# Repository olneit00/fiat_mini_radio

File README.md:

# PipER32 – Mini-Radio für den Fiat 500

**PipER32** ist ein kompaktes, selbst gebautes Internetradio im Stil klassischer Autoradios der 1960er-Jahre. Das Projekt verbindet ein individuell konstruiertes, 3D-druckbares Gehäuse mit moderner Elektronik und einer bewusst zurückhaltenden Retro-Optik.

Das Gerät ist für den Einbau in einen kleinen vorhandenen Aschenbecher-Schacht eines historischen Fiat 500 gedacht. Die Konstruktion kann auch als Ausgangspunkt für andere kompakte Einbauten dienen.

> **Projektstatus (November 2026):** CAD-Modelle, der yoRadio-basierte Firmware-Quellcode und erste Unterlagen zur Leiterplattenentwicklung sind im Repository vorhanden. Die Elektronik läuft bisher als verdrahteter ESP32-S3-DevKit-Prototyp. Die Dateien in `layout/` sind **DRAFT** und ausdrücklich noch nicht zur Fertigung freigegeben.

## Konzept

- Kompaktes Gehäuse mit separater Front- und Rückwand
- Zwei klassische Drehknöpfe als Bedienelemente
- Kleines Farbdisplay zwischen den Knöpfen
- Internet-Audiowiedergabe über WLAN
- Statische, nostalgisch gestaltete Frequenzskala im Ruhezustand
- Moderne Benutzeroberfläche während der Bedienung
- Selbst entworfene, 3D-druckbare Gehäuseteile

Die Retro-Skala ist **rein dekorativ**: Sie stellt weder einen realen UKW-Empfänger noch eine Abstimmung auf analoge Frequenzen dar. Beim Bedienen erscheint weiterhin die reguläre Benutzeroberfläche.

## Mechanischer Aufbau

Die druckbaren Modelle befinden sich im Verzeichnis [CAD](CAD/).

| Datei | Inhalt |
| --- | --- |
| `01_Grundgehaeuse.stl` | Hauptgehäuse |
| `02_Frontpanel.stl` | Frontplatte |
| `03_Heckpanel.stl` | Rückwand |
| `04_Chromrahmen.stl` | Separater dekorativer Frontrahmen |
| `05_Drehknopf.stl` | Drehknopf |
| `06_Chromring.stl` | Dekorativer Ring für einen Drehknopf |
| `07_Test_010.stl` bis `09_Test_030.stl` | Testmodelle |
| `fiat-radio.solidcraft` | Bearbeitbares CAD-Projekt (Dateiname aus der Entwicklung) |

Die Front ist mehrteilig ausgeführt, damit Zierelemente unabhängig von der Grundplatte gefertigt und oberflächenbehandelt werden können. Die endgültigen Maße, Druckparameter, Toleranzen und Befestigungspunkte sind vor einem Nachbau am CAD-Modell und am eigenen Einbauort zu prüfen.

### Hinweise zum 3D-Druck

Die STL-Dateien lassen sich in einem geeigneten Slicer öffnen. Material, Schichthöhe, Stützstrukturen und Ausrichtung hängen vom eingesetzten Drucker und der späteren Einbausituation ab.

Für den dauerhaften Einsatz im Fahrzeug sind insbesondere hohe Innenraumtemperaturen, UV-Belastung, mechanische Befestigung und ausreichender Abstand zu elektrischen Komponenten zu berücksichtigen. Ein geeigneter Werkstoff ist anhand seiner tatsächlichen Temperaturbeständigkeit auszuwählen.

## Elektronik – Prototyp und geplante eigene Leiterplatte

Das bisherige Hardwarekonzept umfasst:

| Baugruppe | Beschreibung |
| --- | --- |
| Mikrocontroller | ESP32-S3-Entwicklungsboard mit WLAN |
| Display | Kleines ST7789-Farbdisplay über SPI |
| Audioausgabe | Externer I²S-Digital-Analog-Wandler |
| Verstärker | Kompakte Audioverstärkerplatine |
| Bedienung | Zwei Drehencoder, gegebenenfalls mit Drucktastern |
| Stromversorgung | Geregelte Versorgung passend zu den verwendeten Komponenten |

Diese Tabelle beschreibt den bisherigen Aufbau, **keine abschließend verifizierte Stückliste**.

### Displayanschlüsse: frühere Prototypverdrahtung und aktuelle Firmware

Die folgende Tabelle dokumentiert die **früher notierte Prototypverdrahtung** und ist **nicht** mit der aktuellen Firmwarekonfiguration identisch. Für die PCB-Entwicklung gelten zunächst die aktiven Definitionen in `firmware/myoptions.h` (CS=17, DC=16, RST=15). Die SPI-Buspins müssen anhand des verwendeten ESP32-S3-Arduino-Cores noch verifiziert werden.

| Display-Signal | GPIO / Anschluss |
| --- | --- |
| SCL / CLK | GPIO 13 |
| SDA / MOSI | GPIO 14 |
| CS | GPIO 15 |
| DC | GPIO 16 |
| RES / RST | GPIO 17 |
| Hintergrundbeleuchtung | 3,3 V gemäß verwendeter Displayplatine |

Die Firmware definiert außerdem I²S auf GPIO 5/4/6 und zwei Encoder auf GPIO 47/21/7 beziehungsweise 39/40/41. Die tatsächlichen Modulanschlüsse, SPI-Buspins, Versorgung und Footprints müssen noch geprüft werden. **Keinesfalls Anschlüsse allein anhand dieser vorläufigen Tabelle verdrahten.**

## Software und Bedienoberfläche

Der Quellcode liegt jetzt unter [firmware](firmware/). Er basiert auf [yoRadio](https://github.com/e2002/yoradio) und wird für das Mini-Radio angepasst. `firmware/platformio.ini` konfiguriert ein ESP32-S3-DevKitC-1 N16R8 mit 16 MB Flash und 8 MB PSRAM; `firmware/myoptions.h` enthält die projektspezifischen Pinzuordnungen. Der genaue Build- und Teststand sowie die Lizenzhinweise sind vor einem Nachbau zu prüfen.

Vorgesehen beziehungsweise im bisherigen Prototyp erprobt:

- Empfang von Internet-Audiostreams über WLAN
- Bedienung über zwei Drehencoder
- Anzeige von Sender- und Statusinformationen
- Automatischer Wechsel zu einer Retro-Anzeige bei Inaktivität
- Rückkehr zur regulären Benutzeroberfläche bei Bedienung

### Retro-Anzeige

Der Ruhezustand orientiert sich allgemein an beleuchteten Analogskalen der 1960er-Jahre:

- Elfenbeinfarbener Hintergrund
- Dunkle Skalenmarkierungen und Ziffern
- Fester roter Abstimmzeiger
- Dezente, gleichmäßige Beleuchtungswirkung

Die Skala ist als **statisches Designmotiv** vorgesehen. Der Zeiger bewegt sich nicht mit der Senderauswahl und es werden keine Internetsender auf analoge Frequenzen abgebildet. Damit bleibt die vorhandene Steuerung unabhängig vom dekorativen Erscheinungsbild.

## PCB-Entwicklung (DRAFT)

Unter [layout](layout/) liegen erste Arbeitsdateien zur eigenen Leiterplatte: vorläufige Netzliste, GPIO-Pinmapping, Stückliste, KiCad-Vorbereitungstabellen, Bauteilhinweise und ein Layout-Leitfaden. Diese Unterlagen sind **noch kein vollständiger KiCad-Schaltplan** und nicht zur Produktion freigegeben.

Für die Platine ist ein ESP32-S3-WROOM-1-Modul statt des bisherigen DevBoards vorgesehen. Vor der Umsetzung sind insbesondere die tatsächlichen SPI-Leitungen, die Versorgung von Display/DAC/Verstärker, USB-Programmierung, Boot-/Reset-Schaltung, Antennenfreiraum und die mechanischen Einbaumaße zu klären.

## Repository-Struktur

| Verzeichnis | Inhalt | Stand |
| --- | --- | --- |
| [`CAD/`](CAD/) | STL-Modelle und SolidCraft-Projekt | Vorhanden |
| [`firmware/`](firmware/) | yoRadio-basierter Quellcode, Konfiguration und Webressourcen | In Entwicklung |
| [`layout/`](layout/) | Pinmapping, Netzliste, BOM und PCB-Planung | **DRAFT** |

## Nächste Schritte

- [x] Firmwarestand in das Repository aufnehmen
- [ ] Abhängigkeiten und Open-Source-Lizenzen prüfen und dokumentieren
- [ ] Finale Pinbelegung aller Baugruppen ergänzen
- [ ] Stückliste und Stromversorgung dokumentieren
- [ ] Build- und Flash-Anleitung anhand des tatsächlichen Quellcodes erstellen
- [ ] Tastenfunktionen sowie Verhalten bei kurzem und langem Tastendruck verifizieren
- [ ] Fotos, Einbaumaße und Druckhinweise ergänzen
- [ ] Darstellung der Retro-Skala mit dem finalen Display abgleichen

## Sicherheit und rechtliche Hinweise

Dies ist ein privates Maker- und Dokumentationsprojekt, **kein offizielles oder von einem Fahrzeug- oder Gerätehersteller unterstütztes Produkt**. Die Gestaltung ist eigenständig und lediglich allgemein von der Ästhetik historischer Geräte inspiriert. Fremde Logos, Wortmarken, originale Skalenabbildungen und geschützte Grafiken sind nicht Bestandteil dieser Dokumentation.

**Software-Lizenzen:** Fremde Software und Bibliotheken behalten ihre jeweiligen Lizenzbedingungen. Bei Änderungen und Weitergabe der bereits enthaltenen Firmware müssen vorhandene Urheberrechtshinweise, Lizenztexte und gegebenenfalls Hinweise auf Änderungen korrekt übernommen werden. Für eigene Inhalte wurde noch keine Lizenz festgelegt; daraus ergibt sich keine pauschale Erlaubnis zur Weiterverwendung.

**Zugangsdaten:** Keine Passwörter, WLAN-Zugangsdaten, API-Schlüssel oder Zugriffstoken einchecken. Lokale Konfigurationen vor dem Veröffentlichen kontrollieren. Bereits offengelegte Zugangsdaten unverzüglich widerrufen.

**Einbau und Betrieb:** Anschlüsse elektrisch absichern, die Spannungsversorgung auf mögliche Fahrzeugspannungsschwankungen auslegen und den Einbau so gestalten, dass weder Bedienung noch Fahrzeugsicherheit beeinträchtigt werden. Die bereitgestellten Dateien und Angaben erfolgen ohne Gewähr; Nachbau und Betrieb erfolgen in eigener Verantwortung.

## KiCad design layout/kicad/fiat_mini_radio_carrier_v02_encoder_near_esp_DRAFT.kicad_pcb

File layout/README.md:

# PipER32 – PCB-Layout – DRAFT v0.4: rein passive Trägerplatine

**Ziel:** So einfach wie möglich. Die Platine enthält **keine aktiven Komponenten** und keine eigenen Widerstände, Spannungsregler, USB-Buchsen oder Taster. **Noch nicht fertigungsreif.**

## Mechanische Zielgröße
- **PCB-Zielmaß: 70 × 70 mm** (Nutzerwunsch, noch nicht auf Passform verifiziert).
- ESP32-Header: 2 × 22 Kontakte, 2,54-mm-Raster angenommen, Reihenabstand 24,5 mm Mitte–Mitte vom Nutzer gemessen.
- ESP32-Modul mit vorhandenen angelöteten Stiftleisten, daher Buchsenleisten auf Trägerplatine.
- Zwei USB-C-Buchsen befinden sich auf dem vorhandenen ESP32-Board; keine Buchse auf der Trägerplatine.
- DAC-Modulabmessungen, Position und Gehäusefreiheit noch offen.

## Bestückung
1. Zwei **22-polige Buchsenleisten (2 × 22 Kontakte)** als Sockel für das **vorhandene ESP32-S3-DevKitC-1 N16R8** (USB-C sitzt bereits auf dem DevKit).
2. Eine **6-polige Buchsenleiste** für das vorhandene **PCM5100-DAC-Modul** (Pinfolge VIN, GND, LCK, DIN, BCK, SCK).
3. **Durchkontaktierte, beschriftete Lötaugen** für Encoder 1 (A, B, SW, GND).
4. **Durchkontaktierte, beschriftete Lötaugen** für Encoder 2 (A, B, SW, GND).
5. **Durchkontaktierte, beschriftete Lötaugen** für das ST7789-Display (VCC, GND, SCLK, MOSI, CS, DC, RST, BLK soweit das konkrete Modul sie benötigt).

Keine Verstärkerschaltung. Audioausgänge bleiben zunächst am vorhandenen DAC-Modul, kein separater Line-Out-Stecker auf der Trägerplatine.

## Stromversorgung
- Ein einziges USB-C-Kabel direkt in die Buchse des ESP32-DevKits.
- 3V3 und GND vom DevKit werden passiv an die benötigten Lötaugen verteilt.
- **DAC-VIN ist bis zur Prüfung der zulässigen Versorgungsspannung des konkreten Moduls noch offen.**
- Keine zusätzliche Gehäusebuchse und kein 12-V-Eingang.

## Signalbelegung aus aktueller Firmware
| Verbraucher | Signal | GPIO |
|---|---|---|
| PCM5100 | LCK | 6 |
| PCM5100 | DIN | 5 |
| PCM5100 | BCK | 4 |
| PCM5100 | SCK | GND (vom Nutzer bestätigt) |
| Encoder 1 | A, B, SW | 47, 21, 7 |
| Encoder 2 | A, B, SW | 39, 40, 41 |
| ST7789 | CS, DC, RST | 17, 16, 15 |
| ST7789 | SCLK, MOSI | noch mit tatsächlich genutztem SPI2/HSPI-Core abgleichen |

## Dateien
- [schaltplan_v02.md](schaltplan_v02.md) – ältere Architekturübersicht, teils überholt; **diese README v0.4 hat Vorrang**
- [pcm5100_module.md](pcm5100_module.md) – DAC-Modul und Pinfolge
- [pin_mapping.csv](pin_mapping.csv) – Firmwarebelegung
- [schaltplan_netzliste.csv](schaltplan_netzliste.csv) – vorläufig, nicht vollständig
- [bom.csv](bom.csv) – ältere Stückliste, für v0.4 zu reduzieren
- [kicad_pin_assignment.csv](kicad_pin_assignment.csv) – ältere KiCad-Vorbereitung

## Vor dem Layout zwingend abgleichen
- Stiftleistenanzahl **22 je Seite (vom Nutzer bestätigt)**. Pitch voraussichtlich 2,54 mm; **Reihenabstand Mitte–Mitte der Pinreihen vom Nutzer erneut gemessen: 24,5 mm** (abweichend von manchen Espressif-Referenzboards). Orientierung noch prüfen. Vor Fertigung mit einem Probeausdruck 1:1 oder der realen Platine verifizieren.
- Stiftabstand, Maße und Einsteckrichtung des PCM5100-Moduls.
- Stromversorgung und BLK-Beschaltung des Displaymoduls.
- Die **tatsächlichen** SPI-SCLK/MOSI-Pins der laufenden Firmware.
- Lage der Kabel-Lötaugen im CAD-Gehäuse und Antennenfreiraum des ESP32.

**Nächster Schritt:** Maßzeichnung/Footprints der beiden Steckmodule festlegen, anschließend passive KiCad-Schaltplan- und PCB-Dateien erzeugen.

## Drehencoder verdrahten

Siehe [Encoder-Verdrahtung](encoder_verdrahtung.md) für die vieradrige Verbindung, lokale GND-Brücke zwischen Encoder-C und Taster sowie Empfehlungen für steckbare Anschlüsse und Zugentlastung.

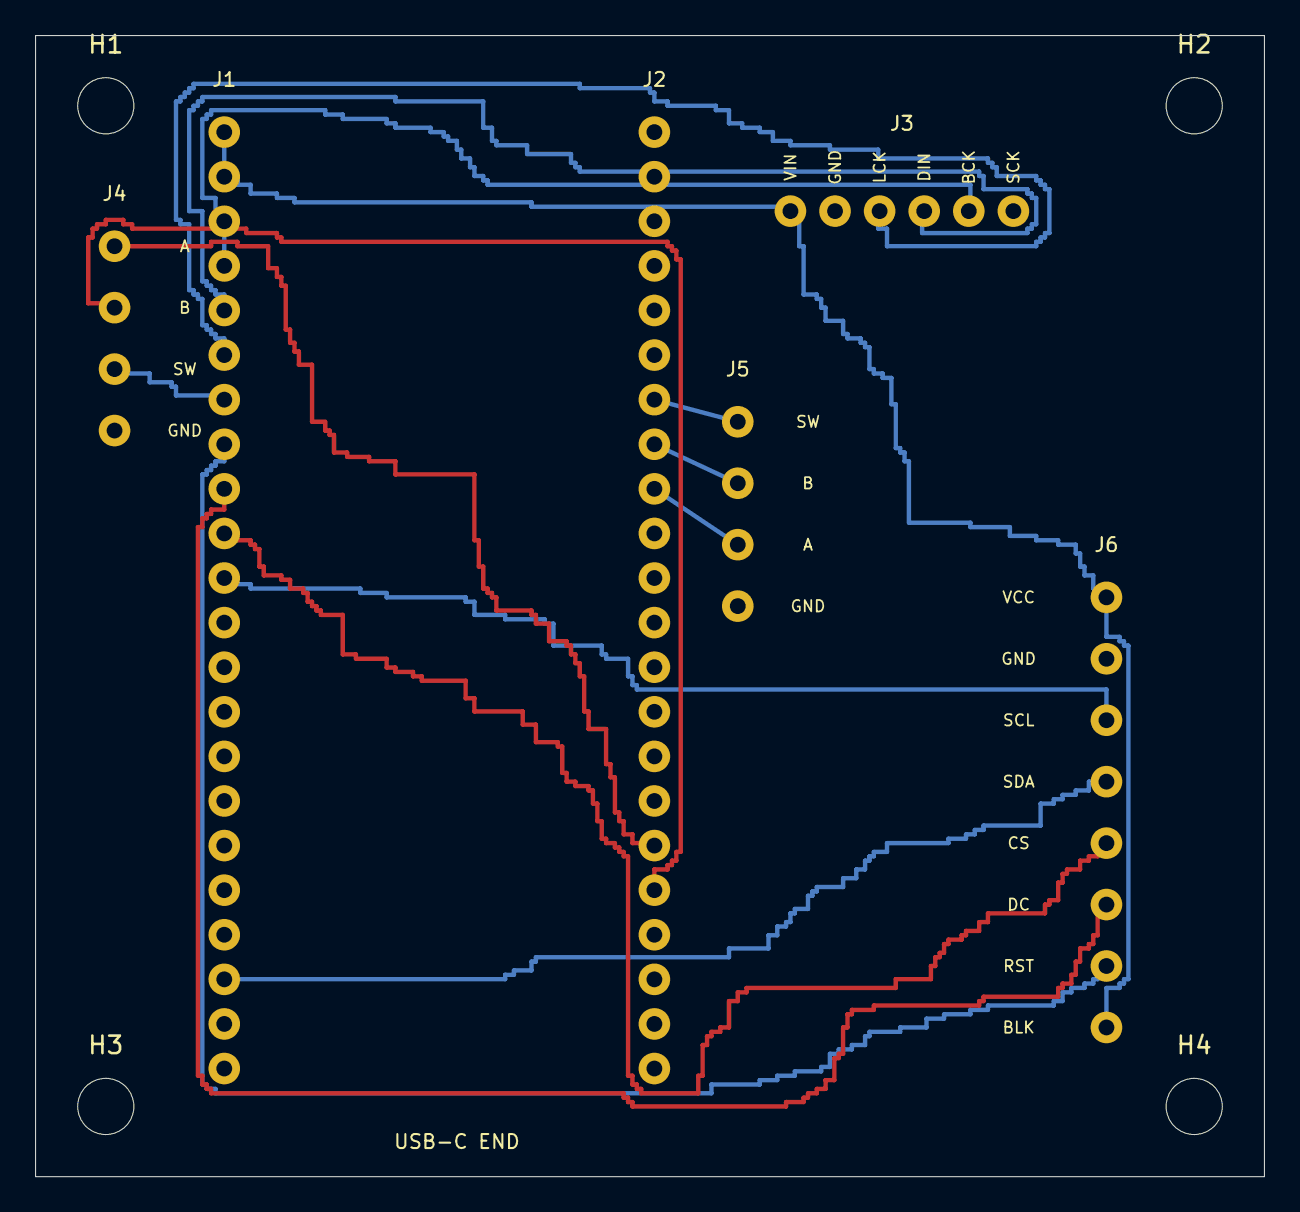
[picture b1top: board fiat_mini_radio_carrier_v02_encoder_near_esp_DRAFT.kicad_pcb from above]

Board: 2 copper layers, 70.0 x 65.0 mm, 10 parts (0 on the bottom side), 16 nets.

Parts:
H1, H2, H3, H4: MountingHole_3.2mm_M3
J1, J2: ESP32_22; PinSocket_1x22_P2.54mm_Vertical
J3: PCM5102A_SHORT_EDGE; PinSocket_1x06_P2.54mm_Vertical
J4, J5: ENCODER; SolderPads_1x4
J6: ST7789; SolderPads_1x8

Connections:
3V3: J1.1, J1.2, J3.1, J6.1, J6.8
GND: J1.22, J2.1, J2.21, J2.22, J3.2, J3.6, J4.4, J5.4, J6.2
GPIO4: J1.4, J3.5
GPIO5: J1.5, J3.4
GPIO6: J1.6, J3.3
GPIO7: J1.7, J4.3
GPIO14: J1.20, J6.4
GPIO15: J1.8, J6.7
GPIO16: J1.9, J6.6
GPIO17: J1.10, J6.5
GPIO18: J1.11, J6.3
GPIO21: J2.18, J4.2
GPIO39: J2.9, J5.3
GPIO40: J2.8, J5.2
GPIO41: J2.7, J5.1
GPIO47: J2.17, J4.1
